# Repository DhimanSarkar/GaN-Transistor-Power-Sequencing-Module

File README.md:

<h1 align="center" id="title">GaN Power Supply Sequencing Module</h1>

<h2>🧐 Features</h2>

Here're some of the project's best features:

*   Vdd = 28V
*   Vgg= [-2,-5]V

<h2>🛡️ License:</h2>

This project is licensed under the CERN-OHL-S and GNU-GPL-3.0

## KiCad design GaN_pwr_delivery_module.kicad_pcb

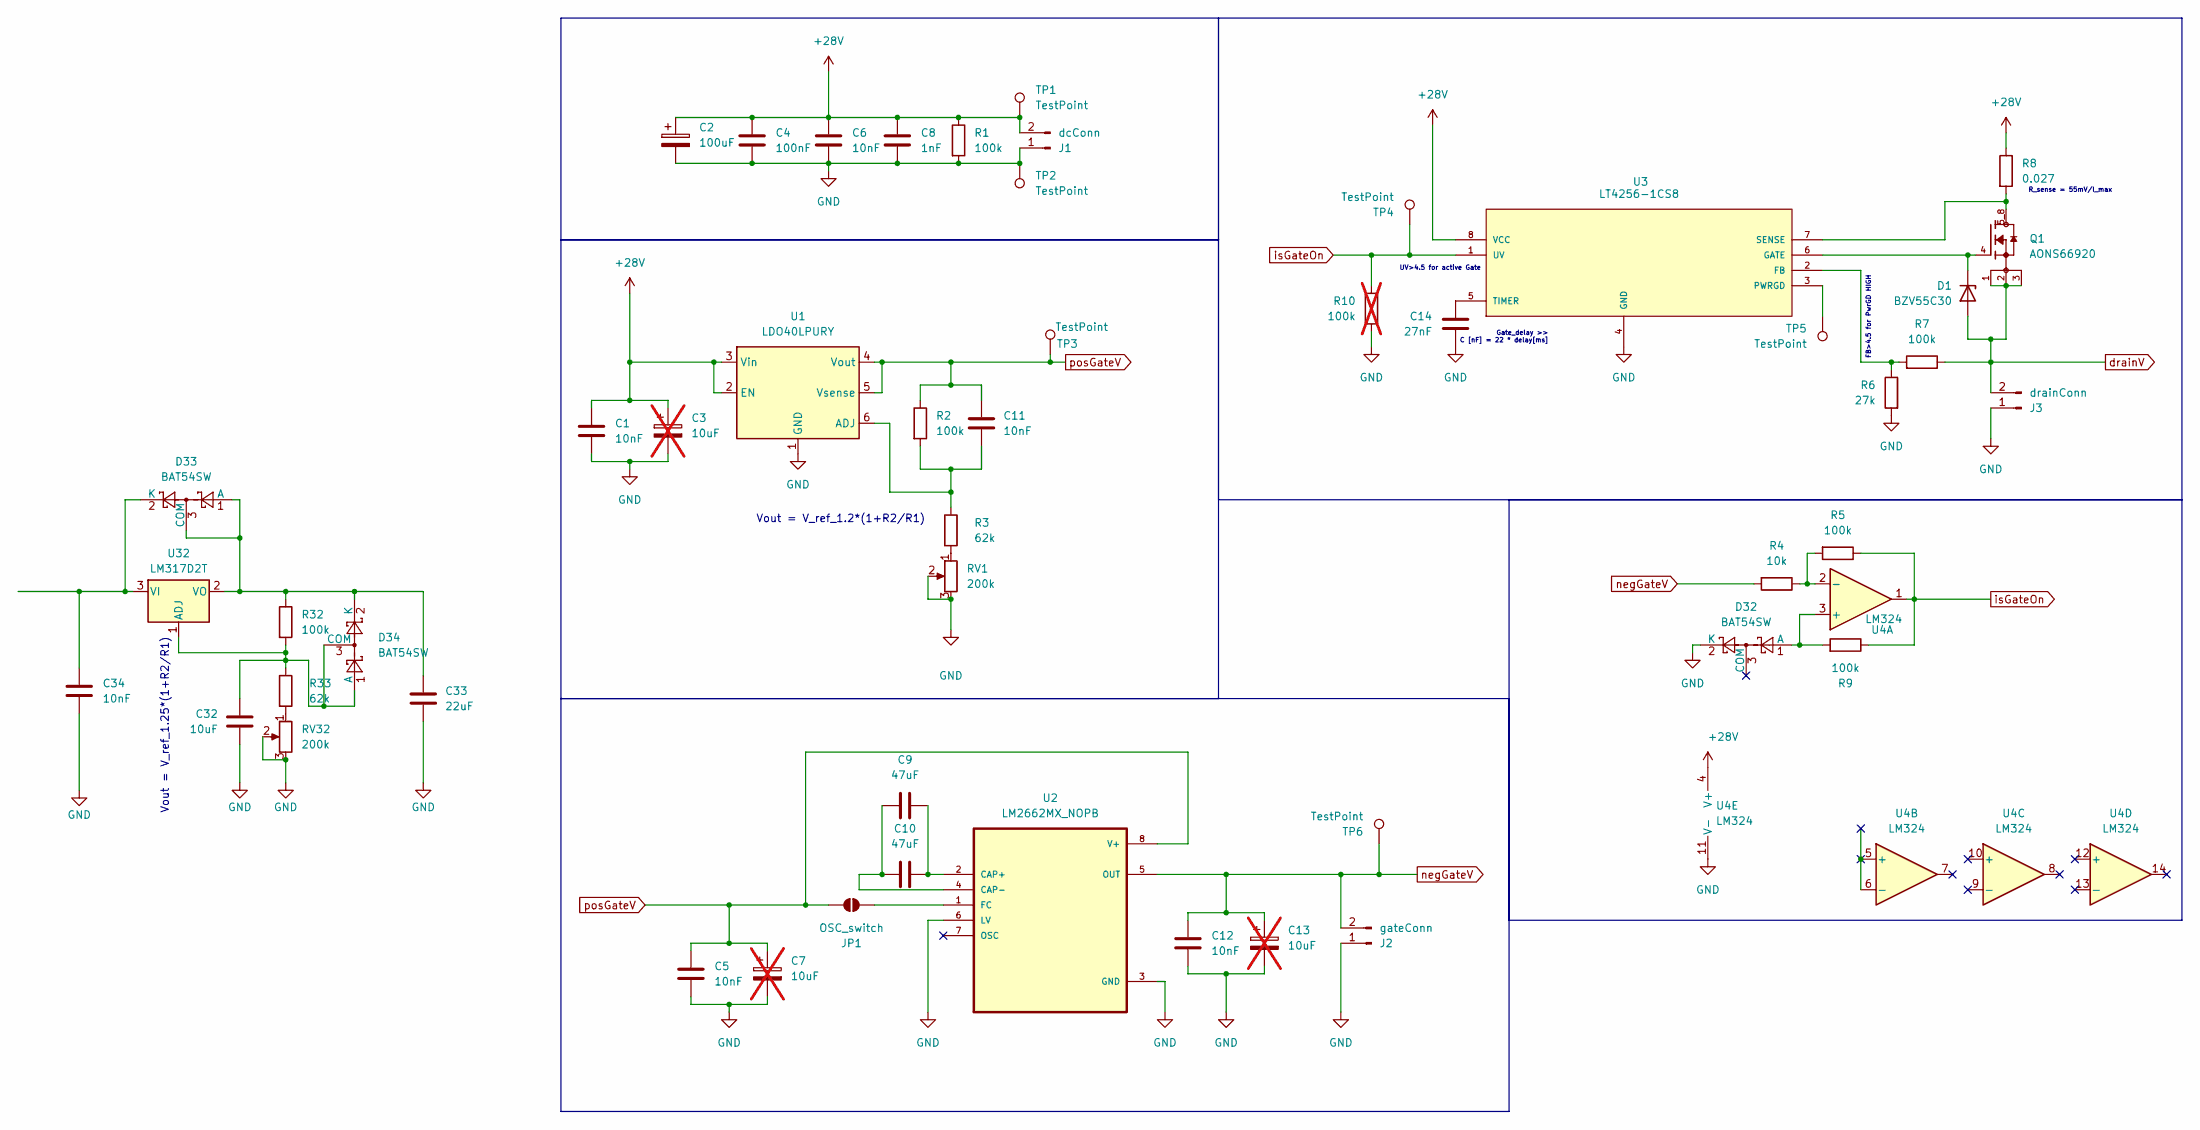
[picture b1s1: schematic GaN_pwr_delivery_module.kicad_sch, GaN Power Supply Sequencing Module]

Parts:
C1, C5, C12, C34: 10nF; C_0805_2012Metric_Pad1.18x1.45mm_HandSolder
C2: 100uF; CP_Elec_6.3x9.9
C3, C7, C13: 10uF; CP_Elec_6.3x9.9; not fitted
C4: 100nF; C_0805_2012Metric
C6, C11: 10nF; C_0805_2012Metric
C8: 1nF; C_0805_2012Metric
C9, C10: 47uF; C_0805_2012Metric_Pad1.18x1.45mm_HandSolder
C14: 27nF; C_0805_2012Metric_Pad1.18x1.45mm_HandSolder
C32: 10uF; CP_Elec_6.3x9.9
C33: 22uF; CP_Elec_6.3x9.9
D1: BZV55C30; D_MiniMELF
D32, D33, D34: BAT54SW; SOT-323_SC-70
J1: dcConn; SolderWire-0.1sqmm_1x02_P3.6mm_D0.4mm_OD1mm
J2: gateConn; SolderWire-0.1sqmm_1x02_P3.6mm_D0.4mm_OD1mm
J3: drainConn; SolderWire-0.1sqmm_1x02_P3.6mm_D0.4mm_OD1mm
JP1: OSC_switch; SolderJumper-2_P1.3mm_Open_RoundedPad1.0x1.5mm
Q1: AONS66920; TRANS_AONS66920; PARTREV 1.0
R1, R2, R5, R7, R9, R32: 100k; R_0805_2012Metric
R3, R33: 62k; R_0805_2012Metric
R4: 10k; R_0805_2012Metric
R6: 27k; R_0805_2012Metric
R8: 0.027; R_0805_2012Metric
R10: 100k; R_0805_2012Metric; not fitted
RV1, RV32: 200k; Potentiometer_Bourns_3296W_Vertical
TP1, TP2, TP3, TP4, TP5, TP6: TestPoint; TestPoint_Pad_D1.5mm
U1: LDO40LPURY; DFN-6-1EP_3x3mm_P0.95mm_EP1.7x2.6mm
U2: LM2662MX_NOPB; SOIC127P599X175-8N
U3: LT4256-1CS8; SO-8_S; MANUFACTURER_PART_NUMBER LT42561CS8
U4: LM324; SOIC127P600X175-14N
U32: LM317D2T; VREG_L7805ACD2T

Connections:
+28V: C1.1, C2.1, C3.1, C4.1, C6.1, C8.1, J1.2, R1.1, R8.1, TP1.1, U1.2 (EN), U1.3 (Vin), U3.8 (VCC), U4.4 (V+)
GND: C1.2, C2.2, C3.2, C4.2, C5.2, C6.2, C7.2, C8.2, C12.2, C13.2, C14.2, C32.2, C33.2, C34.2, D32.2 (K), J1.1, J2.1, J3.1, R1.2, R6.2, R10.2, RV1.2, RV1.3, RV32.2, RV32.3, TP2.1, U1.1 (GND), U1.7 (GND), U2.3 (GND), U2.6 (LV), U3.4 (GND), U4.11 (V-)
unnamed: D1.1 (K), Q1.4, U3.6 (GATE)
unnamed: D32.1 (A), R9.2, U4.3 (+)
unnamed: C33.1, D33.1 (A), D33.3 (COM), D34.2 (K), R32.1, U32.2 (VO)
unnamed: C34.1, D33.2 (K), U32.3 (VI)
unnamed: C32.1, D34.1 (A), D34.3 (COM), R32.2, R33.1, U32.1 (ADJ)
unnamed: JP1.2 (B), U2.1 (FC)
unnamed: R3.2, RV1.1
unnamed: R33.2, RV32.1
unnamed: C11.2, R2.2, R3.1, U1.6 (ADJ)
unnamed: C9.2, C10.2, U2.2 (CAP+)
unnamed: C9.1, C10.1, U2.4 (CAP-)
unnamed: R6.1, R7.2, U3.2 (FB)
unnamed: TP5.1, U3.3 (PWRGD)
unnamed: Q1.5_8, R8.2, U3.7 (SENSE)
unnamed: C14.1, U3.5 (TIMER)
unnamed: R4.1, R5.2, U4.2 (-)
drainV: D1.2 (A), J3.2, Q1.1, Q1.2, Q1.3, R7.1
isGateOn: R5.1, R9.1, R10.1, TP4.1, U3.1 (UV), U4.1
negGateV: C12.1, C13.1, J2.2, R4.2, TP6.1, U2.5 (OUT)
posGateV: C5.1, C7.1, C11.1, JP1.1 (A), R2.1, TP3.1, U1.4 (Vout), U1.5 (Vsense), U2.8 (V+)

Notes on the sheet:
UV>4.5 for active Gate
Vout = V_ref_1.25*(1+R2/R1)
Vout = V_ref_1.2*(1+R2/R1)
Gate_delay >> C [nF] = 22 * delay[ms]
FB>4.5 for PwrGD HIGH
R_sense = 55mV/I_max

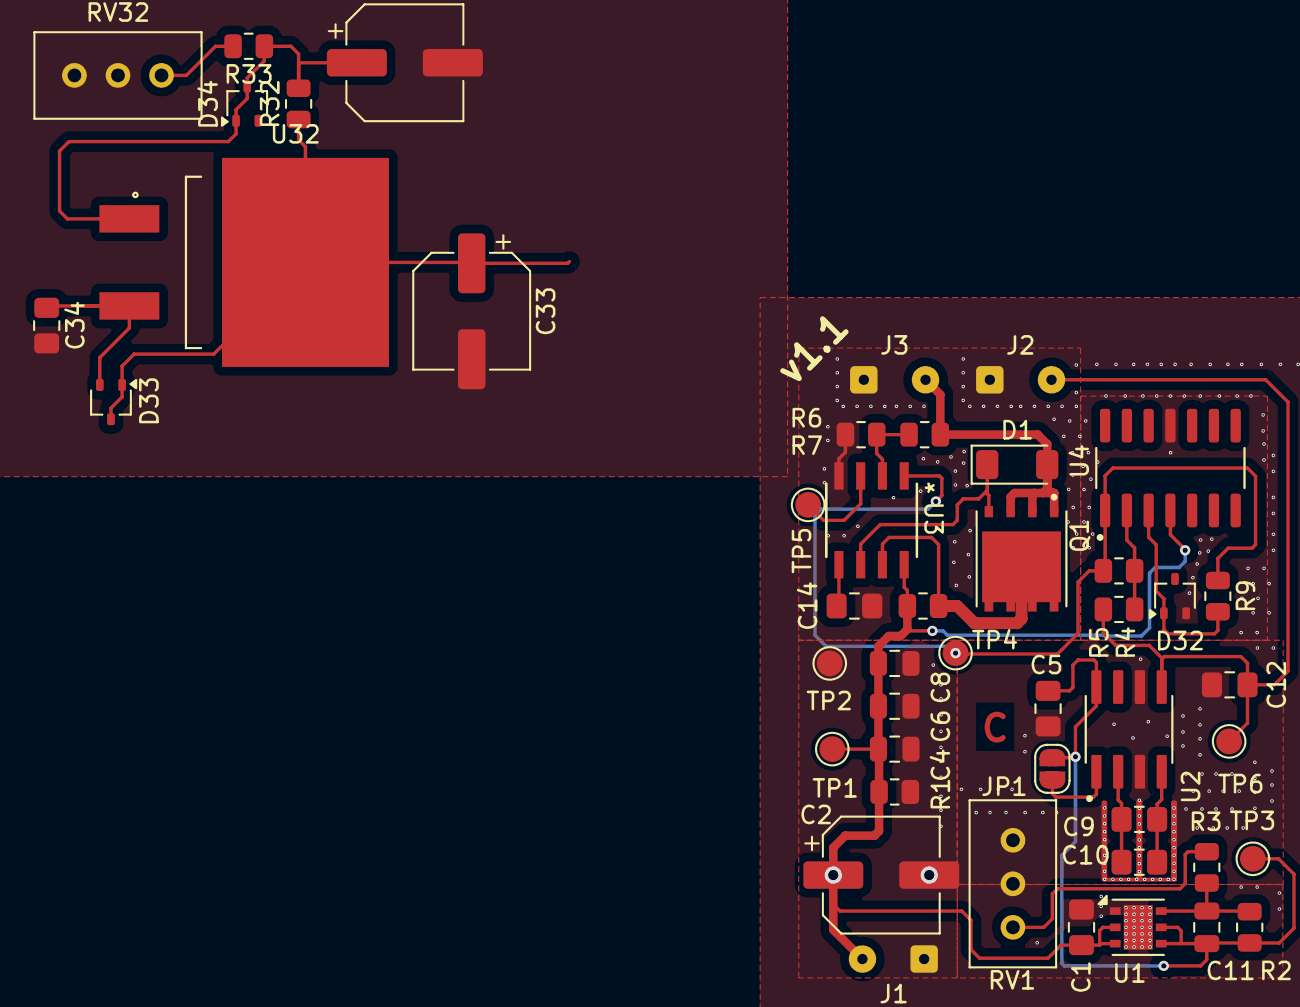
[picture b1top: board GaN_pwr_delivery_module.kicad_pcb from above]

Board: 2 copper layers, 47 parts (0 on the bottom side), 22 nets.

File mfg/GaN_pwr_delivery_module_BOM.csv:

"Reference","Value","Footprint","Datasheet","Qty","DNP"
"C1,C5,C12","10nF","Capacitor_SMD:C_0805_2012Metric_Pad1.18x1.45mm_HandSolder","~","3",""
"C2,C7","100uF","Capacitor_SMD:CP_Elec_3x5.3","~","2",""
"C3,C13","100uF","Capacitor_SMD:CP_Elec_3x5.3","~","2","DNP"
"C4","100nF","Capacitor_SMD:C_0805_2012Metric","~","1",""
"C6,C11","10nF","Capacitor_SMD:C_0805_2012Metric","~","2",""
"C8","1nF","Capacitor_SMD:C_0805_2012Metric","~","1",""
"C9,C10","47uF","Capacitor_SMD:C_0805_2012Metric_Pad1.18x1.45mm_HandSolder","~","2",""
"C14","27nF","Capacitor_SMD:C_0805_2012Metric_Pad1.18x1.45mm_HandSolder","~","1",""
"D1","BZV55C30","Diode_SMD:D_MiniMELF","https://assets.nexperia.com/documents/data-sheet/BZV55_SER.pdf","1",""
"D32","BAT54SW","Package_TO_SOT_SMD:SOT-323_SC-70","https://assets.nexperia.com/documents/data-sheet/BAT54W_SER.pdf","1",""
"J1","dcConn","Connector_Wire:SolderWire-0.1sqmm_1x02_P3.6mm_D0.4mm_OD1mm","~","1",""
"J2","gateConn","Connector_Wire:SolderWire-0.1sqmm_1x02_P3.6mm_D0.4mm_OD1mm","~","1",""
"J3","drainConn","Connector_Wire:SolderWire-0.1sqmm_1x02_P3.6mm_D0.4mm_OD1mm","~","1",""
"JP1","OSC_switch","Jumper:SolderJumper-2_P1.3mm_Open_RoundedPad1.0x1.5mm","~","1",""
"Q1","AONS66920","AONS66920:TRANS_AONS66920","","1",""
"R1,R2,R5,R7,R9","100k","Resistor_SMD:R_0805_2012Metric","~","5",""
"R3","62k","Resistor_SMD:R_0805_2012Metric","~","1",""
"R4","10k","Resistor_SMD:R_0805_2012Metric","~","1",""
"R6","27k","Resistor_SMD:R_0805_2012Metric","~","1",""
"R8","0.027","Resistor_SMD:R_0805_2012Metric","~","1",""
"RV1","200k","Potentiometer_THT:Potentiometer_Bourns_3296W_Vertical","~","1",""
"TP1,TP2,TP3,TP4,TP5","TestPoint","TestPoint:TestPoint_Pad_D1.5mm","~","5",""
"U1","LDO40LPURY","Package_DFN_QFN:DFN-6-1EP_3x3mm_P0.95mm_EP1.7x2.6mm","https://www.st.com/resource/en/datasheet/ldo40l.pdf","1",""
"U2","LM2662MX_NOPB","LM2662MX_NOPB:SOIC127P599X175-8N","","1",""
"U3","LT4256-1CS8","LT4256-1CS8:SO-8_S","","1",""
"U4","LM324","LM324DRG3:SOIC127P600X175-14N","http://www.ti.com/lit/ds/symlink/lm2902-n.pdf","1",""

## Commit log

2025-05-01 init
2025-05-01 LICENSE
2025-05-01 Project specific symbols, footprints, 3D models, simulation models, and datasheets.
2025-05-01 initial ideas
2025-05-04 init ideas
2025-05-04 init pcb
2025-05-04 oshw template
2025-05-05 ltspice gitignore
2025-05-05 sim files
2025-05-21 init idea
2025-05-21 BOM tracking added
2025-05-22 BOM location changed
2025-05-22 mfg gerber
2025-05-22 cap lib
